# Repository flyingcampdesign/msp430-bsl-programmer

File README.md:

View this project on [CADLAB.io](https://cadlab.io/project/1186). 

MSP430 BSL Programmer
=====================

http://www.flyingcampdesign.com/msp430-bsl-programmer.html

FCD-PRG01
---------

The FCD-PRG01 is a USB bootstrap loader (BSL) programmer for the Texas Instruments MSP430 microprocessor. For designs where low cost or small form factor prohibit the integration of custom programming logic or a large JTAG header, the FCD-PRG01 enables in-system programming by including a single 6 pin header in the target device design.

Originally designed to work with the cross platform TinyOS toolchain, the FCD-PRG01 provides an open source, cross platform alternative to platform dependent development tools for the MSP430 microprocessor.

The FCD-PRG01 integrates a USB-to-serial converter and on board regulated power supply into a small USB dongle, allowing programming and test capability over a single interface. It exposes a standard 6 pin, 0.1” header which can be used to interface to the target board via a device specific cable harness. This modular approach provides designers with the flexibility to select the optimal physical programming interface for the unique design constraints of each target platform.

FCD-CBL01
---------

Programming cable harness which mates with standard 3x2, 2mm PCB headers. (See
FCD-PRG01 datasheet and header footprint Eagle library for details)

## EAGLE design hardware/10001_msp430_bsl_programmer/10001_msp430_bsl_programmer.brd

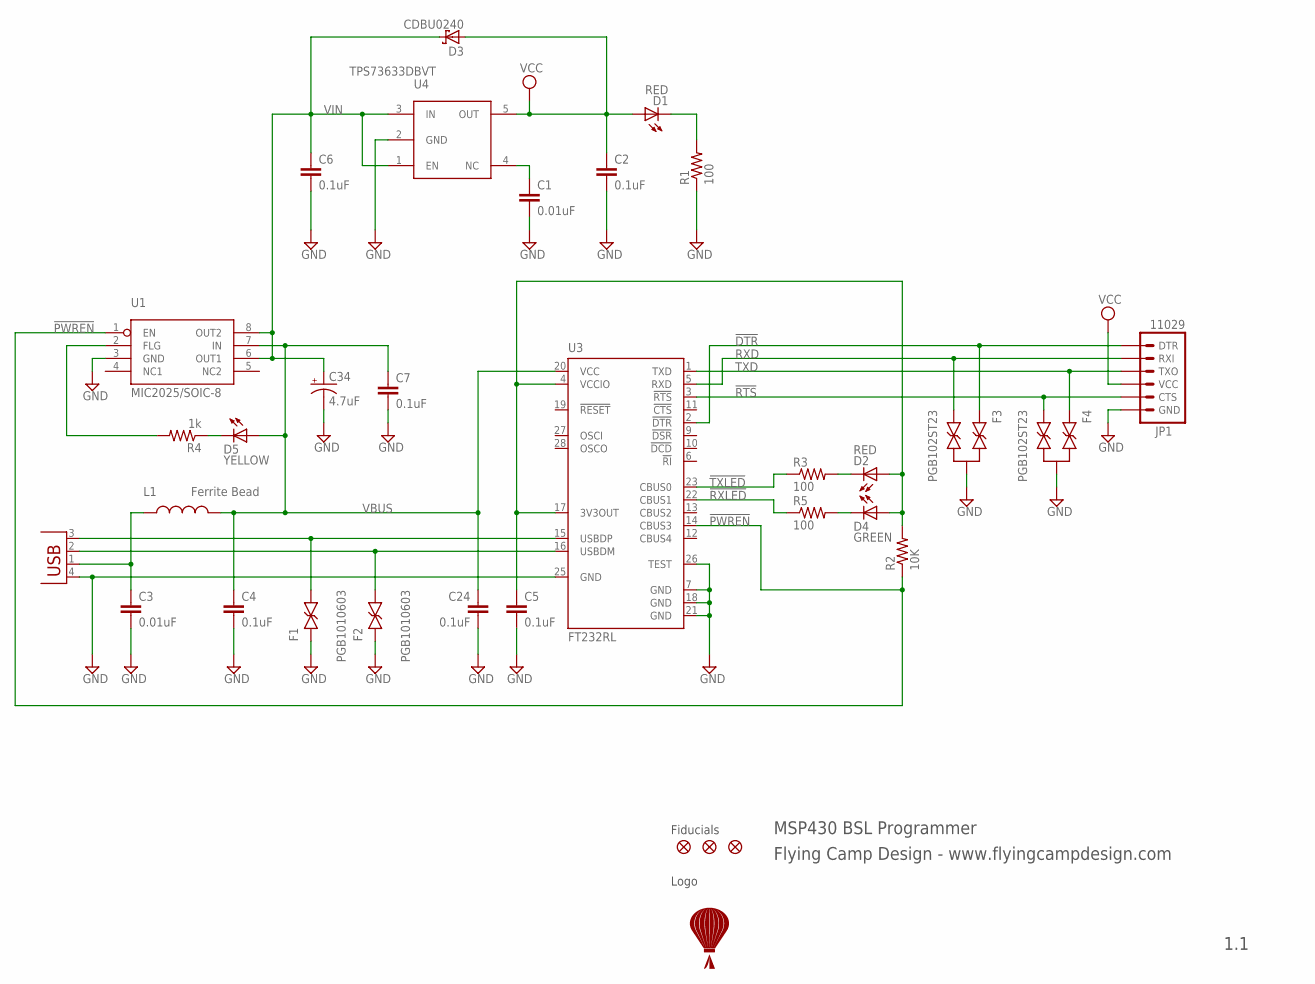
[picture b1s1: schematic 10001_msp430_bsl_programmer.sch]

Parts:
C1, C3: 0.01uF; CAPC1608
C2, C4, C5, C6, C7, C24: 0.1uF; CAPC1608
C34: 4.7uF; EIA3216
D1, D2: RED; LEDC1608
D3: CDBU0240; D0603
D4: GREEN; LEDC1608
D5: YELLOW; LEDC1608
F1, F2: PGB1010603; CAPC1608
F3, F4: PGB102ST23; SOT23
JP1: 11029; 1X06-SMD
L1: Ferrite Bead; 0603
P1: MOLEX_48037-1000
R1, R3, R5: 100; RESC1608
R2: 10K; RESC1608
R4: 1k; RESC1608
U1: MIC2025/SOIC-8; SOIC-8
U3: FT232RL; SSOP28
U4: TPS73633DBVT; SOT95P280-5
U$1: FLYING_CAMP_DESIGN_LOGO
U$2, U$3, U$4: FIDUCIAL1X2; FIDUCIAL-1X2

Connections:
!DTR: F3.1, JP1.1 (DTR), U3.2 (!DTR)
!PWREN: R2.1, U1.1 (EN), U3.14 (CBUS3)
!RTS: F4.2, JP1.5 (CTS), U3.3 (!RTS)
!RXLED: R5.1, U3.22 (CBUS1)
!TXLED: R3.1, U3.23 (CBUS0)
D+: F1.2, P1.3 (D+), U3.15 (USBDP)
D-: F2.2, P1.2 (D-), U3.16 (USBDM)
GND: C1.2, C2.2, C3.2, C4.2, C5.2, C6.2, C7.2, C24.2, C34.C (-), F1.1, F2.1, F3.3, F4.3, JP1.6 (GND), P1.4 (GND), R1.1, U1.3 (GND), U3.7 (GND), U3.18 (GND), U3.21 (GND), U3.25 (GND), U3.26 (TEST), U4.2 (GND)
unnamed: D1.C, R1.2
unnamed: C1.1, U4.4 (NC)
unnamed: R4.2, U1.2 (FLG)
unnamed: D5.C, R4.1
unnamed: D2.C, R3.2
unnamed: D4.C, R5.2
RXD: F3.2, JP1.2 (RXI), U3.5 (RXD)
TXD: F4.1, JP1.3 (TXO), U3.1 (TXD)
VBUS: C4.1, C7.1, C24.1, D5.A, L1.2, U1.7 (IN), U3.20 (VCC)
VCC: C2.1, D1.A, D3.A, JP1.4 (VCC), U4.5 (OUT)
VCCIO: C5.1, D2.A, D4.A, R2.2, U3.4 (VCCIO), U3.17 (3V3OUT)
VIN: C6.1, C34.A (+), D3.C, U1.6 (OUT1), U1.8 (OUT2), U4.1 (EN), U4.3 (IN)
VUSB: C3.1, L1.1, P1.1 (VBUS)

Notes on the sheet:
MSP430 BSL Programmer
1.1
Fiducials
Flying Camp Design - www.flyingcampdesign.com
Logo

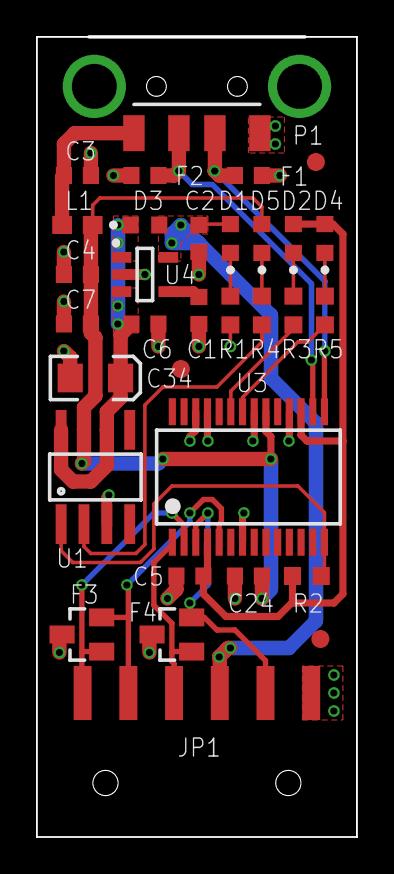
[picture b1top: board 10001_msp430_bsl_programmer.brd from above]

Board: 2 copper layers, 17.8 x 44.5 mm, 33 parts (1 on the bottom side), 21 nets.

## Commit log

2012-02-13 Add original "doc" dir
2012-12-09 Update FCD-PRG01 datasheet to Rev C
2012-12-09 Initial release of FCD-PRG01 and FCD-CBL01
2012-12-09 Add product page link to readme
2012-12-09 Add EEPROM factory defaults config for FCD-PRG01
2012-12-09 Add FCD-PRG01 labels
2012-12-11 Move doc to docs
2012-12-11 Update FCD-PRG01 datasheet to Rev D
2013-02-10 Move releases into individual release dirs
2013-02-10 Update FCD-PRG01 datasheet to Rev E
2013-02-11 Update FCD-PRG01 datasheet to Rev F
2014-08-12 Add enclosure STEP file
2018-06-20 Backlink to CADLAB.io has been added.
2018-06-21 Update EAGLE files to XML format
2018-06-21 Add .gitignore
2018-06-21 Add EAGLE project files
2022-12-03 Remove old links
